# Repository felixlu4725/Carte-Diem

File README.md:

# Carte Diem - Smart Shopping Cart 

## [Product Demo Video](https://youtu.be/1DGey0mXCpI?si=HsvZ1QVfaDtIknsd)

Carte Diem is a add-on module that integrates smart features to regular carts. This device eliminates the need for checkout lines while maintaining anti-theft features. It’s modularity allows stores to easily implement this technology into the existing ecosystems.

### README Directories
- [PCB](PCB/README.md) — schematics, layout, and power architecture  
- [CAD](CAD/README.md) — mechanical enclosures and mounting hardware
- [cart](cart/README.md) - UI interfacing and backend servers
- [cart_tracking](cart_tracking/README.md) - frontend and backend server for cart tracking
- [Integration](integration/README.md) — ESP32 ↔ Raspberry Pi integration and BLE communication

## Motivation

Despite the widespread adoption of self-checkout, grocery stores still experience congestion, long wait times, and loss-prevention challenges. Existing smart cart solutions address these issues but come at a cost of **$5,000–$10,000 per cart**, making large-scale deployment unrealistic for most retailers.

Carte Diem explores a different design space:
- Retrofit instead of full cart replacement  
- Sensor fusion instead of single-modality detection  
- Real-time embedded verification instead of post-hoc auditing  

The goal is to eliminate checkout lines entirely while maintaining store-side trust, scalability, and cost efficiency.

---

## System Overview

Carte Diem consists of two tightly coupled subsystems:

### On-Cart Embedded System
- **Custom ESP32-S3 PCB** running FreeRTOS
- Interfaces with all sensors and peripherals
- Performs real-time sensing, verification, and event generation
- Communicates with the Raspberry Pi via BLE

### On-Cart Compute + Backend
- **Raspberry Pi 4** provides UI, networking, and payment flow
- Connects to store and Carte Diem servers over WiFi
- Handles inventory queries, checkout confirmation, and analytics upload

---

## Key Features

### Item Detection & Verification
- **Barcode Scanning**
  - Primary item identification method
  - Button- or proximity-triggered
  - Fast and reliable for most items

- **RFID Item Verification**
  - Detects tagged items (e.g., alcohol, high-value goods)
  - Automatically cross-checks cart contents
  - Flags unscanned additions in real time

- **Weight-Based Verification**
  - Four load cells under the cart basket
  - Cross-checks expected vs. measured weight
  - Detects unscanned add/remove events
  - Freezes checkout when inconsistencies are detected

- **Produce Scale**
  - Dedicated top-mounted scale
  - Computes price dynamically based on weight

### Checkout & Security
- **Checkout & Payment**
  - Simulated RFID tap-to-pay
  - QR-code payment flow (Square API)
  - Digital receipt generation

- **GPS-Based Security**
  - Store-defined cart boundaries
  - Alarm triggered if cart exits allowed area

### Analytics & Store Insights
- **Cart Tracking**
  - RFID-based indoor tracking (no computer vision)
  - Generates cart paths and heatmaps
  - Aggregates multi-session shopping behavior

---

## Hardware Architecture

- Custom **ESP32-S3 PCB**
  - UART: barcode scanner, RFID modules
  - SPI: payment RFID
  - I²C: IMU, proximity sensor
  - ADC + GPIO: load cells
  - BLE: ESP32 ↔ Raspberry Pi
- Raspberry Pi 4 with touchscreen display
- Dedicated **12 V LiFePO₄ battery**
- Multi-rail power system (12 V, 9 V, 5 V, 3.3 V, 1.8 V)
- 3D-printed enclosures designed for durability and weather resistance

The system is designed to operate **15+ hours continuously**, matching a full day of store operation.

---

## Software Architecture

- **FreeRTOS-based firmware**
  - Periodic tasks for sensing and monitoring
  - Event-driven verification triggered by weight changes
  - ISR-to-task deferral for responsiveness and power efficiency

- **BLE Communication Protocol**
  - Structured commands for barcode scans, weight readings, RFID bursts, and cart tracking logs

- **Full-Stack Web Backend**
  - Store database and inventory management
  - Cart registration and session tracking
  - Heatmap and path visualization
  - GPS boundary configuration interface

---

## Repository Structure

```text
.
├── CAD/               # Mechanical CAD files for enclosures and mounts
├── PCB/               # Schematics, PCB layouts, and fabrication files
├── cart/              # On-cart UI (Raspberry Pi touchscreen interface)
├── integration/       # ESP32 ↔ Raspberry Pi integration and BLE logic
├── LICENSE            # GPL-3.0 license
└── README.md

```

## Results

- Fully functional prototype demonstrated at the EECS Design Expo
- Reliable real-time detection of item add/remove events using sensor fusion
- Weight-based verification successfully detected unscanned items
- RFID-based cart tracking enabled path reconstruction and heatmap generation
- End-to-end checkout flow validated, including UI, payment simulation, and receipt generation
- Power system met full-day operation targets under worst-case load conditions

## Photo Dump

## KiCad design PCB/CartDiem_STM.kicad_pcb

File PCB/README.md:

# Carte Diem — PCB

This directory contains the **custom ESP32-S3-based PCB** designed for the Carte Diem smart shopping cart system.  
The board serves as the central embedded controller, interfacing with all on-cart sensors, peripherals, and the Raspberry Pi.

---

## Overview

The PCB is responsible for:
- Real-time sensor acquisition
- Item verification and cart state monitoring
- Power distribution and regulation
- BLE communication with the Raspberry Pi

It was designed to support **all-day operation**, modular peripherals, and reliable performance in a noisy retail environment.

---

## Manufractured PCB

## Key Features

- **ESP32-S3 MCU**
  - Runs FreeRTOS
  - Handles sensing, control, and BLE communication

- **Peripheral Interfaces**
  - UART: barcode scanner, item RFID, cart-tracking RFID
  - SPI: payment RFID module
  - I²C: IMU, proximity sensor
  - GPIO + ADC: load cells (via HX711)

- **Power Architecture**
  - 12 V input (external battery)
  - On-board buck and LDO regulation
  - Supports 12 V, 9 V, 5 V, 3.3 V, and 1.8 V rails

- **Connectivity**
  - BLE for bidirectional communication with Raspberry Pi
  - Dedicated connectors for modular sensor attachment

---

## Design Notes

- EMI mitigation was required due to proximity of RFID modules and load cells  
- Power paths were designed conservatively to support peak current draw  
- The board went through multiple revisions to resolve rail shorting and voltage tolerance issues  

---

## Schematic

### Top level

### Power Distribution

### Integrated IMU

### Routing

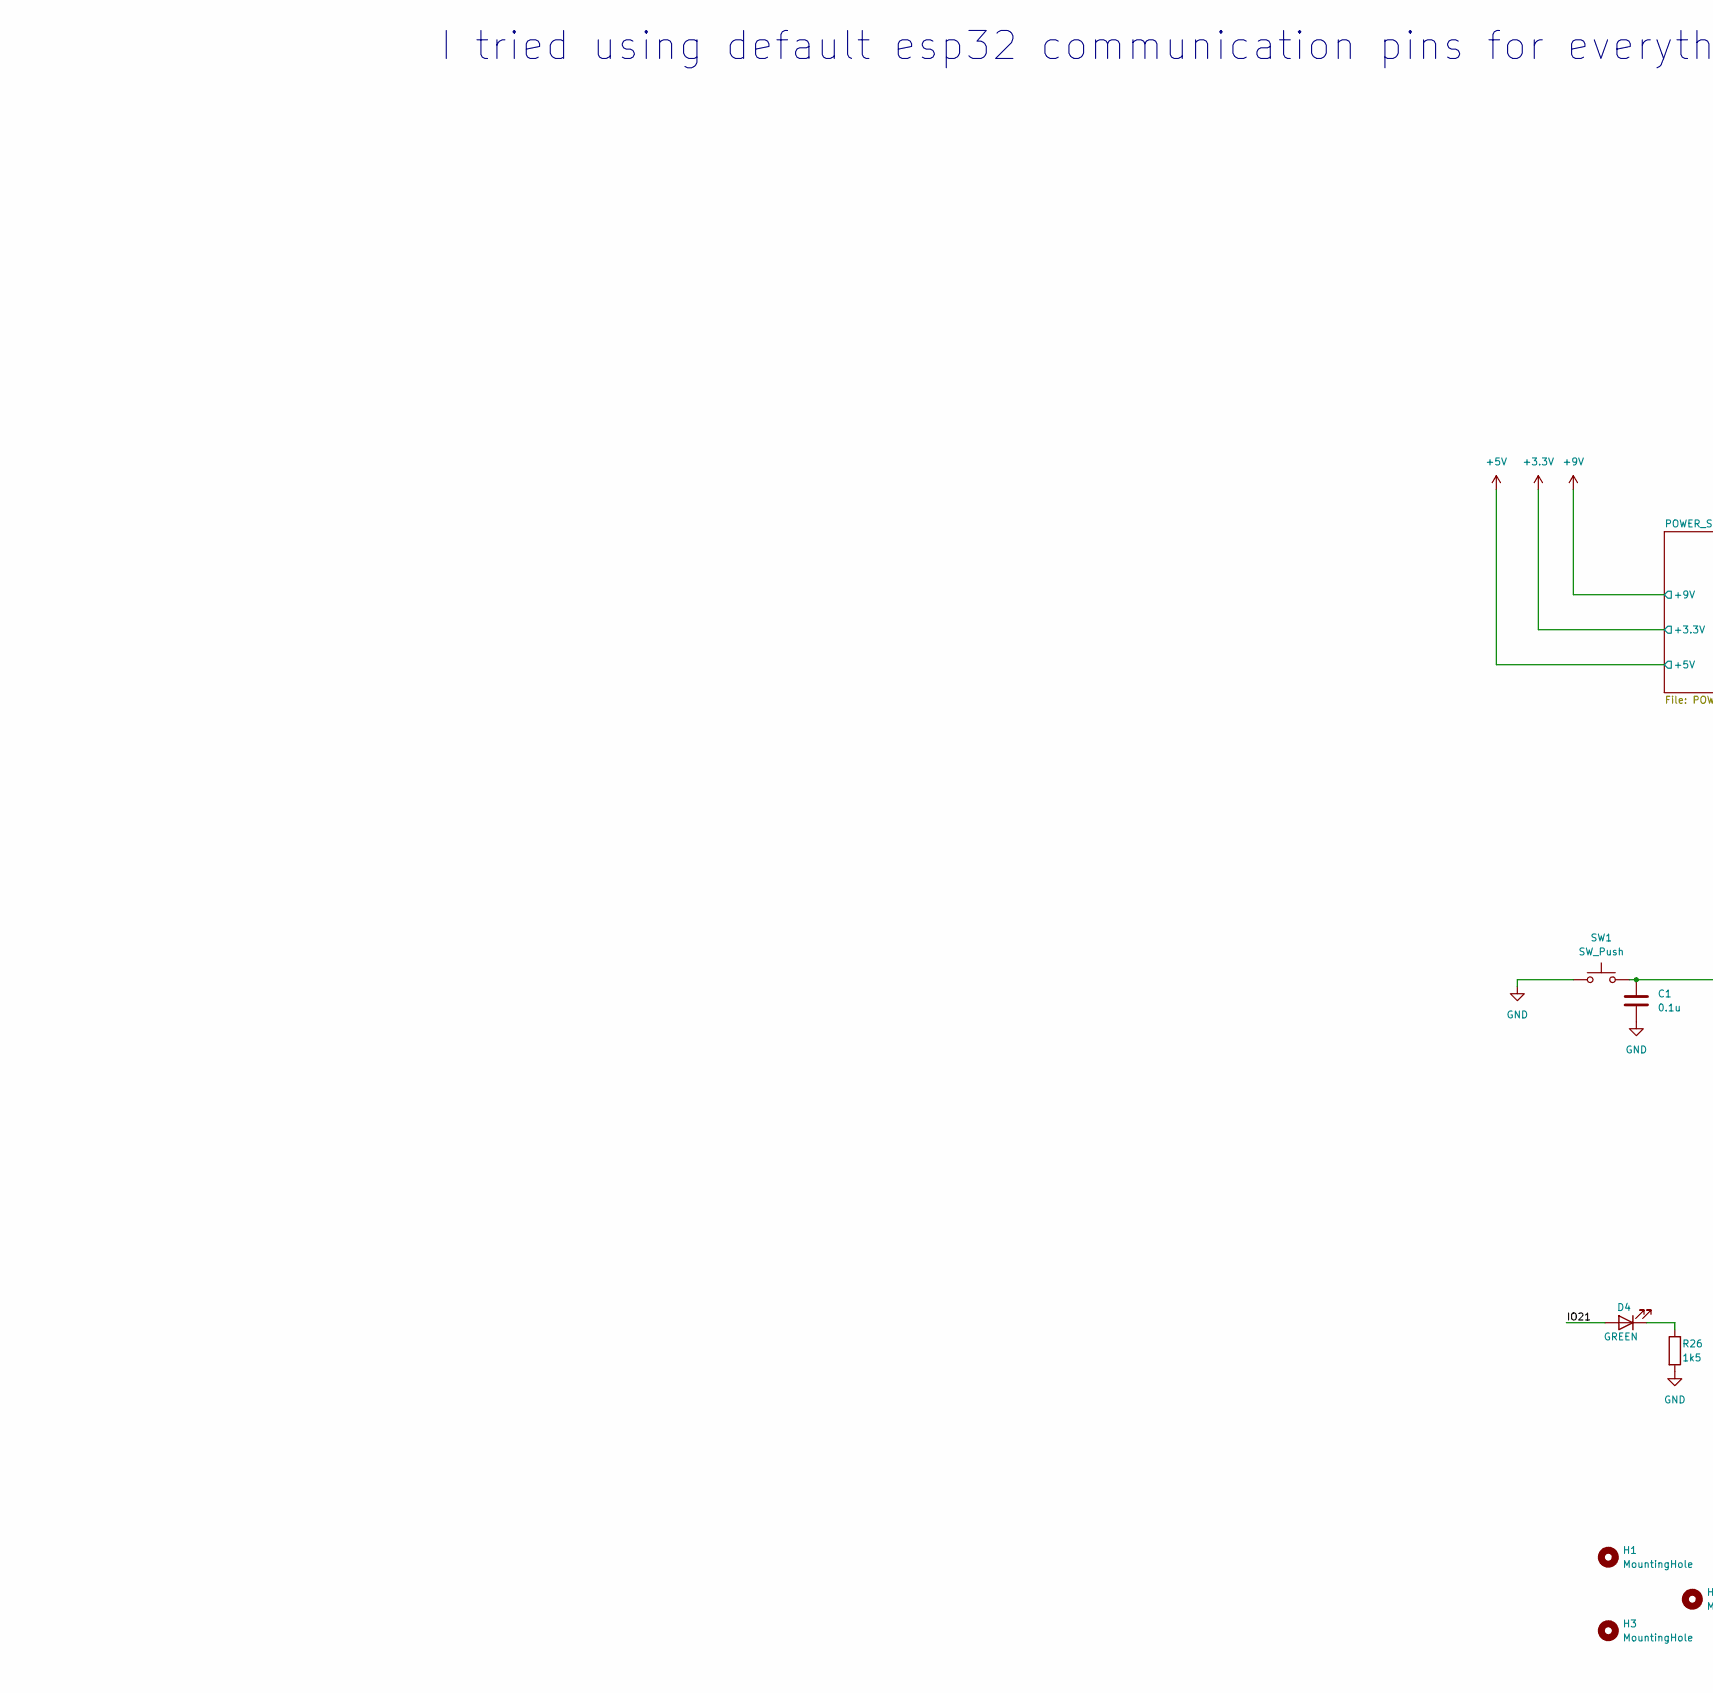
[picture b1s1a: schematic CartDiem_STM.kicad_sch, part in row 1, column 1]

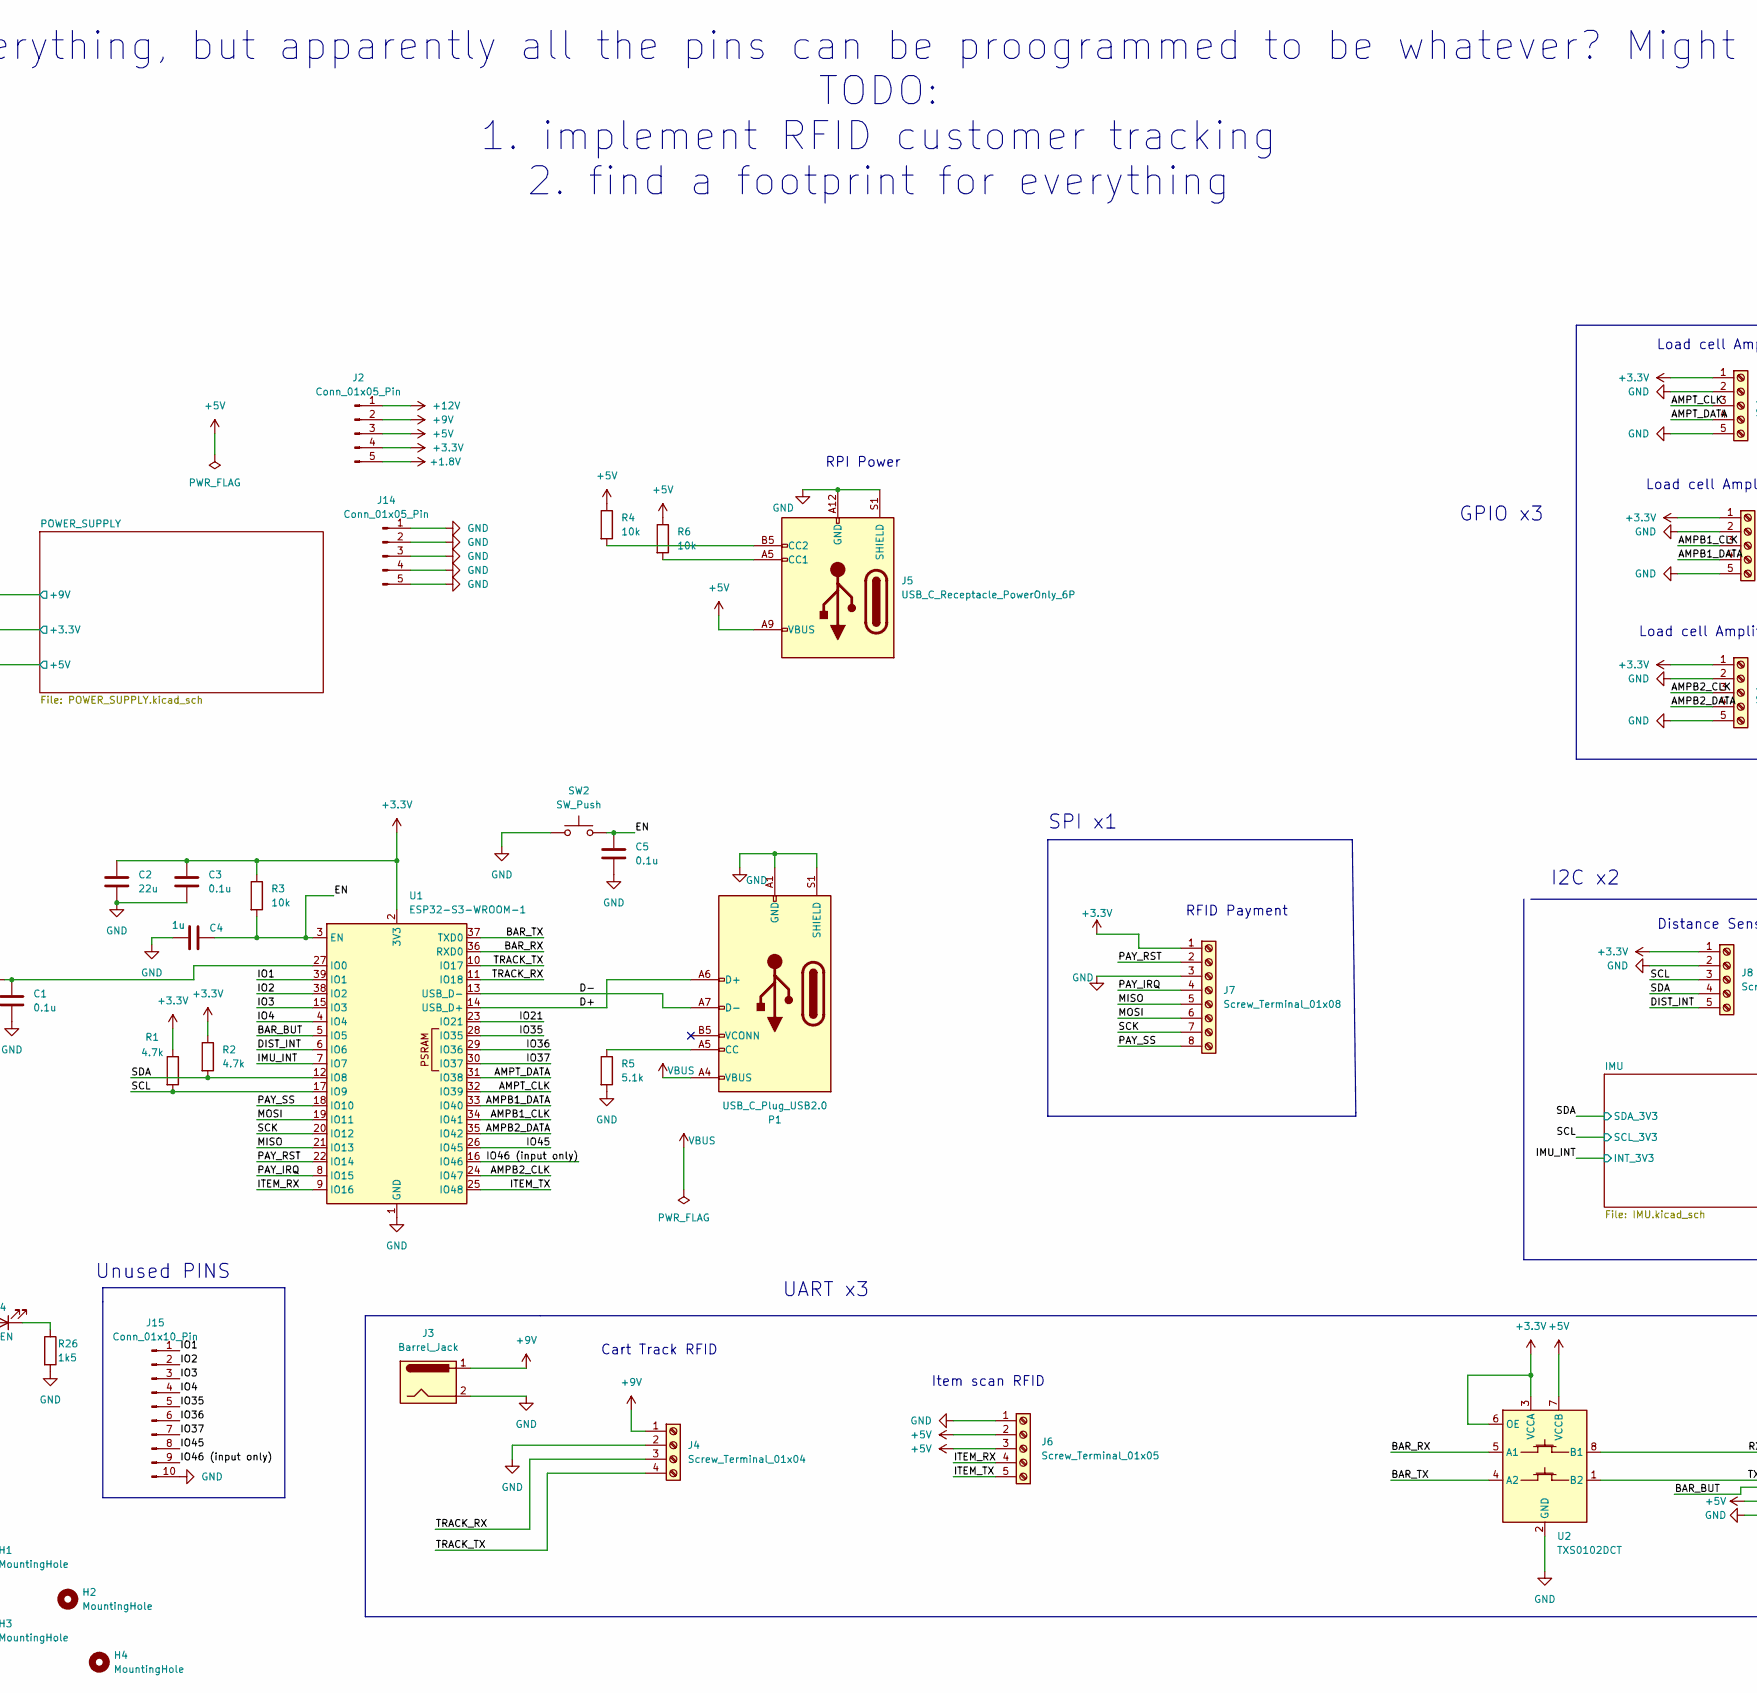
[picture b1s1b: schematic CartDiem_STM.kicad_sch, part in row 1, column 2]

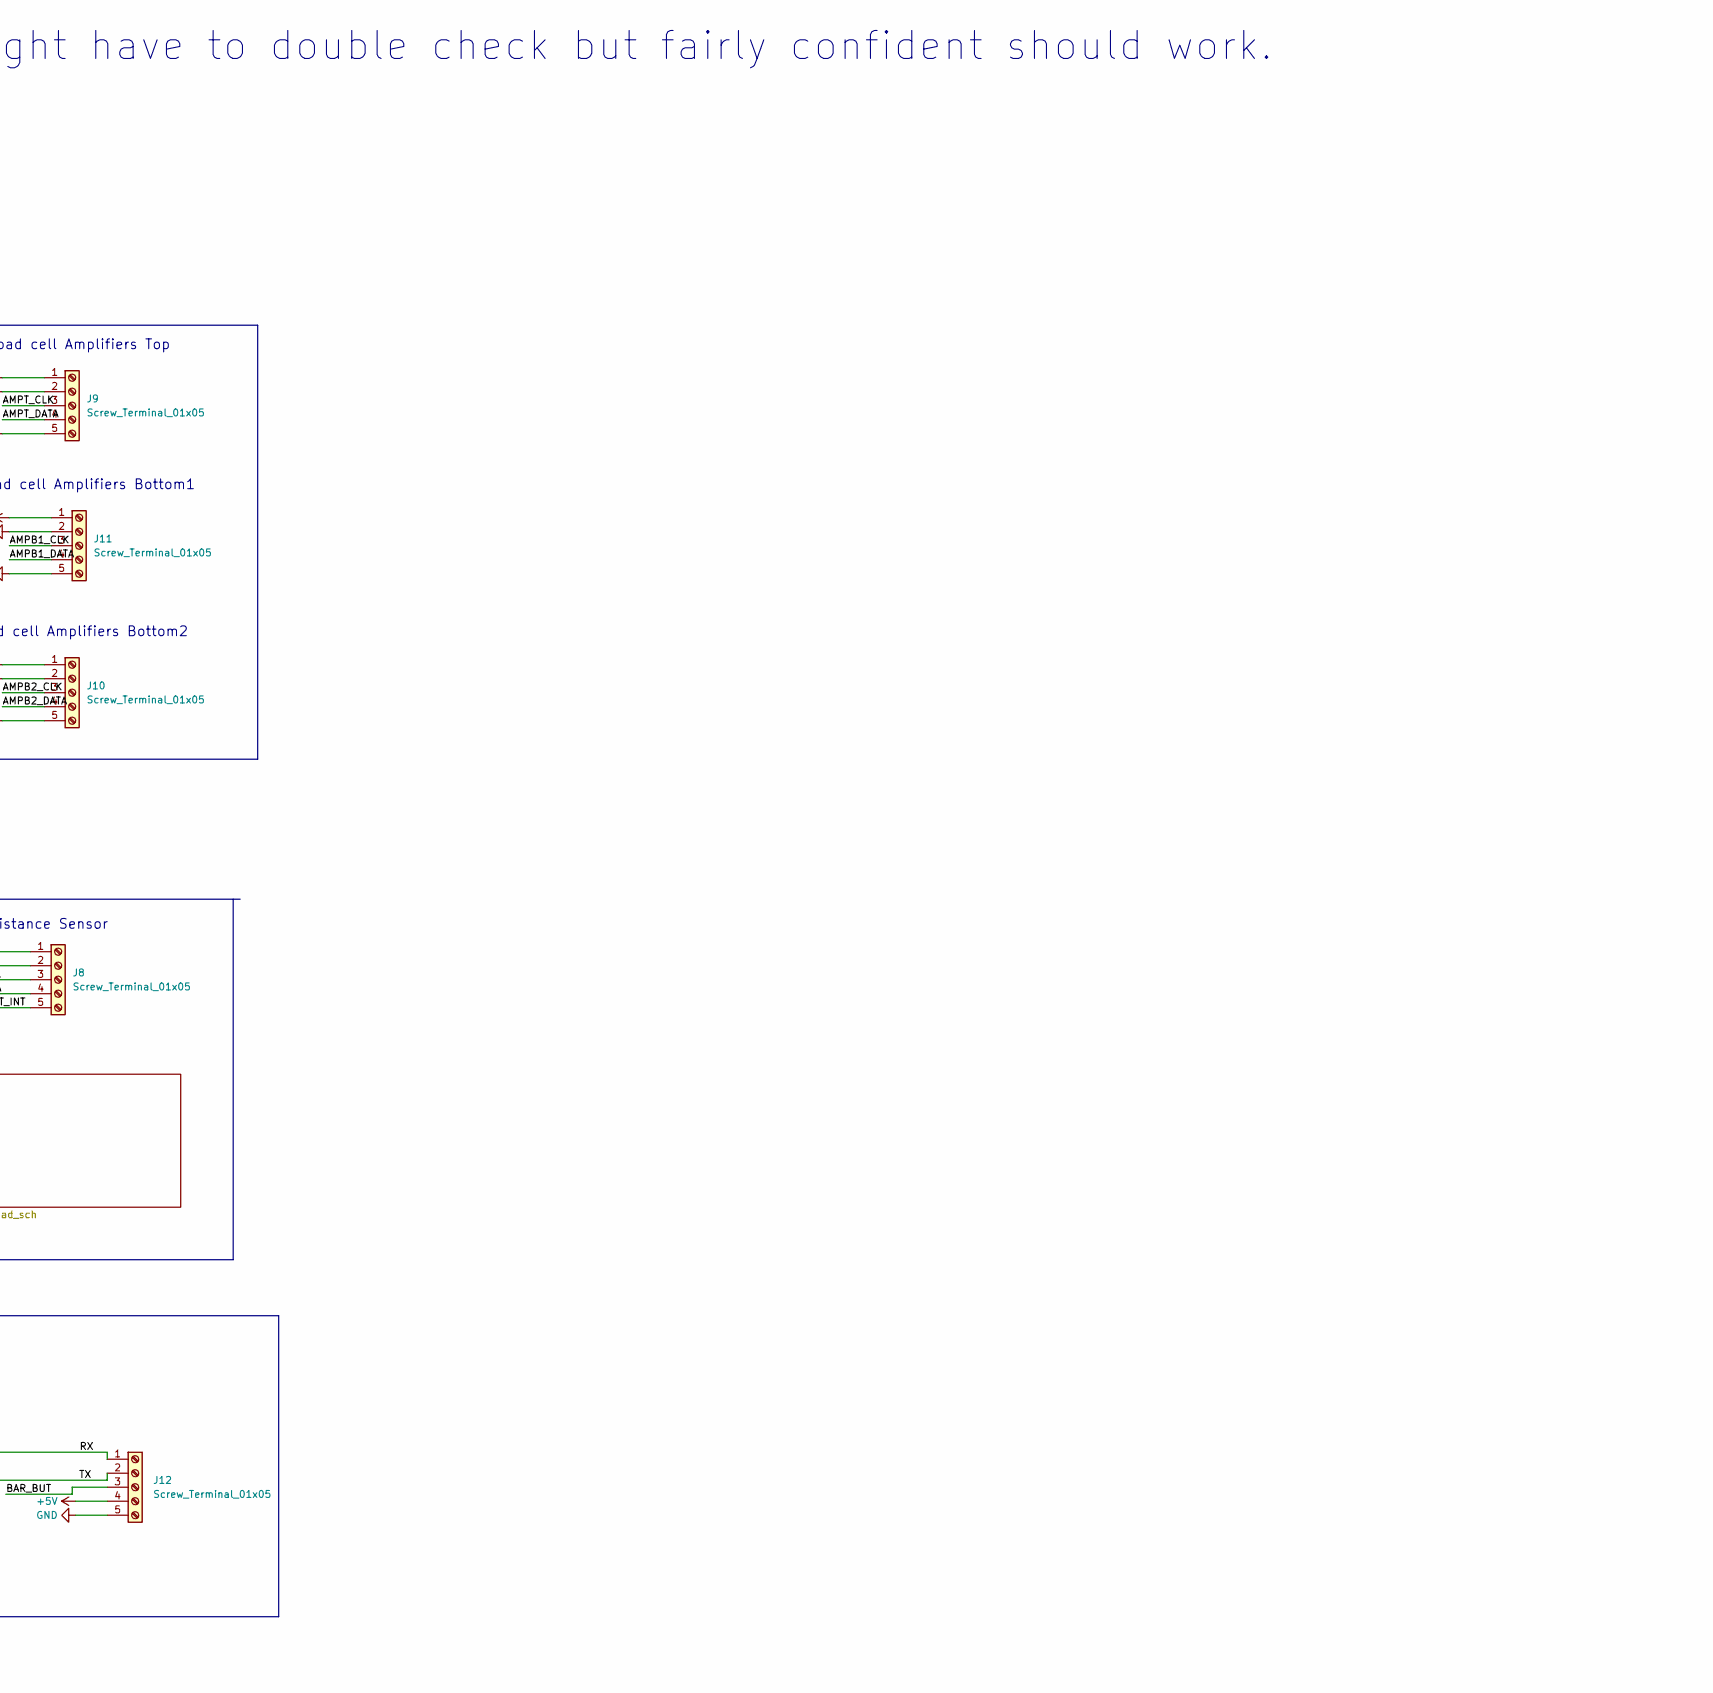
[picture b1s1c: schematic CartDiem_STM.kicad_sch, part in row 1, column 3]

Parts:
C1, C3, C5: 0.1u; C_0603_1608Metric
C2: 22u; C_1210_3225Metric
C4: 1u; C_0603_1608Metric
D4: GREEN; LED_0603_1608Metric
H1, H2, H3, H4: MountingHole; MountingHole_3.2mm_M3
J2, J14: Conn_01x05_Pin; PinHeader_1x05_P2.54mm_Vertical
J3: Barrel_Jack; BarrelJack_CUI_PJ-063AH_Horizontal
J4: Screw_Terminal_01x04; TerminalBlock_Xinya_XY308-2.54-4P_1x04_P2.54mm_Horizontal
J5: USB_C_Receptacle_PowerOnly_6P; USB_C_Receptacle_GCT_USB4125-xx-x-0190_6P_TopMnt_Horizontal
J6, J8, J9, J10, J11, J12: Screw_Terminal_01x05; TerminalBlock_Xinya_XY308-2.54-5P_1x05_P2.54mm_Horizontal
J7: Screw_Terminal_01x08; TerminalBlock_Xinya_XY308-2.54-8P_1x08_P2.54mm_Horizontal
J15: Conn_01x10_Pin; PinHeader_1x10_P2.54mm_Vertical
P1: USB_C_Plug_USB2.0; GCT_USB4120-03-C_REVA
R1, R2: 4.7k; R_0603_1608Metric
R3, R4, R6: 10k; R_0603_1608Metric
R5: 5.1k; R_0603_1608Metric
R26: 1k5; R_0603_1608Metric
SW1, SW2: SW_Push; SW_Push_1P1T_XKB_TS-1187A
U1: ESP32-S3-WROOM-1
U2: TXS0102DCT; SSOP-8_2.95x2.8mm_P0.65mm

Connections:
+1.8V: J2.5; also elsewhere on the board
+3.3V: C2.1, C3.1, J2.4, J7.1, J8.1, J9.1, J10.1, J11.1, R1.1, R2.1, R3.1, U1.2 (3V3), U2.3 (VCCA), U2.6 (OE); also elsewhere on the board
+5V: J2.3, J5.A9 (VBUS), J5.B9 (VBUS), J6.2, J6.3, J12.4, R4.1, R6.1, U2.7 (VCCB); also elsewhere on the board
+9V: J2.2, J3.1, J4.1; also elsewhere on the board
+12V: J2.1; also elsewhere on the board
/AMPB1_CLK: J11.3, U1.34 (IO41)
/AMPB1_DATA: J11.4, U1.33 (IO40)
/AMPB2_CLK: J10.3, U1.24 (IO47)
/AMPB2_DATA: J10.4, U1.35 (IO42)
/AMPT_CLK: J9.3, U1.32 (IO39)
/AMPT_DATA: J9.4, U1.31 (IO38)
/BAR_BUT: J12.3, U1.5 (IO5)
/BAR_RX: U1.36 (RXD0), U2.5 (A1)
/BAR_TX: U1.37 (TXD0), U2.4 (A2)
/D+: P1.A6 (D+), U1.14 (USB_D+)
/D-: P1.A7 (D-), U1.13 (USB_D-)
/DIST_INT: J8.5, U1.6 (IO6)
/EN: C4.2, C5.1, R3.2, SW2.2, U1.3 (EN)
/IMU_INT: U1.7 (IO7); also elsewhere on the board
/IO1: J15.1, U1.39 (IO1)
/IO2: J15.2, U1.38 (IO2)
/IO3: J15.3, U1.15 (IO3)
/IO4: J15.4, U1.4 (IO4)
/IO21: D4.2 (A), U1.23 (IO21)
/IO35: J15.5, U1.28 (IO35)
/IO36: J15.6, U1.29 (IO36)
/IO37: J15.7, U1.30 (IO37)
/IO45: J15.8, U1.26 (IO45)
/IO46 (input only): J15.9, U1.16 (IO46)
/ITEM_RX: J6.4, U1.9 (IO16)
/ITEM_TX: J6.5, U1.25 (IO48)
/MISO: J7.5, U1.21 (IO13)
/MOSI: J7.6, U1.19 (IO11)
/PAY_IRQ: J7.4, U1.8 (IO15)
/PAY_RST: J7.2, U1.22 (IO14)
/PAY_SS: J7.8, U1.18 (IO10)
/RX: J12.1, U2.8 (B1)
/SCK: J7.7, U1.20 (IO12)
/SCL: J8.3, R1.2, U1.17 (IO9); also elsewhere on the board
/SDA: J8.4, R2.2, U1.12 (IO8); also elsewhere on the board
/TRACK_RX: J4.3, U1.11 (IO18)
/TRACK_TX: J4.4, U1.10 (IO17)
/TX: J12.2, U2.1 (B2)
GND: C1.2, C2.2, C3.2, C4.1, C5.2, J3.2, J4.2, J5.A12 (GND), J5.B12 (GND), J5.S1 (SHIELD), J6.1, J7.3, J8.2, J9.2, J9.5, J10.2, J10.5, J11.2, J11.5, J12.5, J14.1, J14.2, J14.3, J14.4, J14.5, J15.10, P1.A1 (GND), P1.A12 (GND), P1.B1 (GND), P1.B12 (GND), P1.S1 (SHIELD), R5.2, R26.2, SW1.1, SW2.1, U1.1 (GND), U1.40 (GND), U1.41 (GND), U2.2 (GND); also elsewhere on the board
unnamed: D4.1 (K), R26.1
unnamed: J5.A5 (CC1), R6.2
unnamed: J5.B5 (CC2), R4.2
unnamed: P1.A5 (CC), R5.1
unnamed: C1.1, SW1.2, U1.27 (IO0)
VBUS: P1.A4 (VBUS), P1.A9 (VBUS), P1.B4 (VBUS), P1.B9 (VBUS); also elsewhere on the board

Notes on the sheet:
Item scan RFID
Unused PINS
Load cell Amplifiers Bottom2
RFID Payment
Cart Track RFID
Distance Sensor
SPI x1
Load cell Amplifiers Bottom1
UART x3
I tried using default esp32 communication pins for everything, but apparently all the pins can be proogrammed to be whatever? Might have to double check but fairly confident should work. TODO: 1. implement RFID customer tracking 2. find a footprint for everything
Load cell Amplifiers Top
GPIO x3
RPI Power
I2C x2

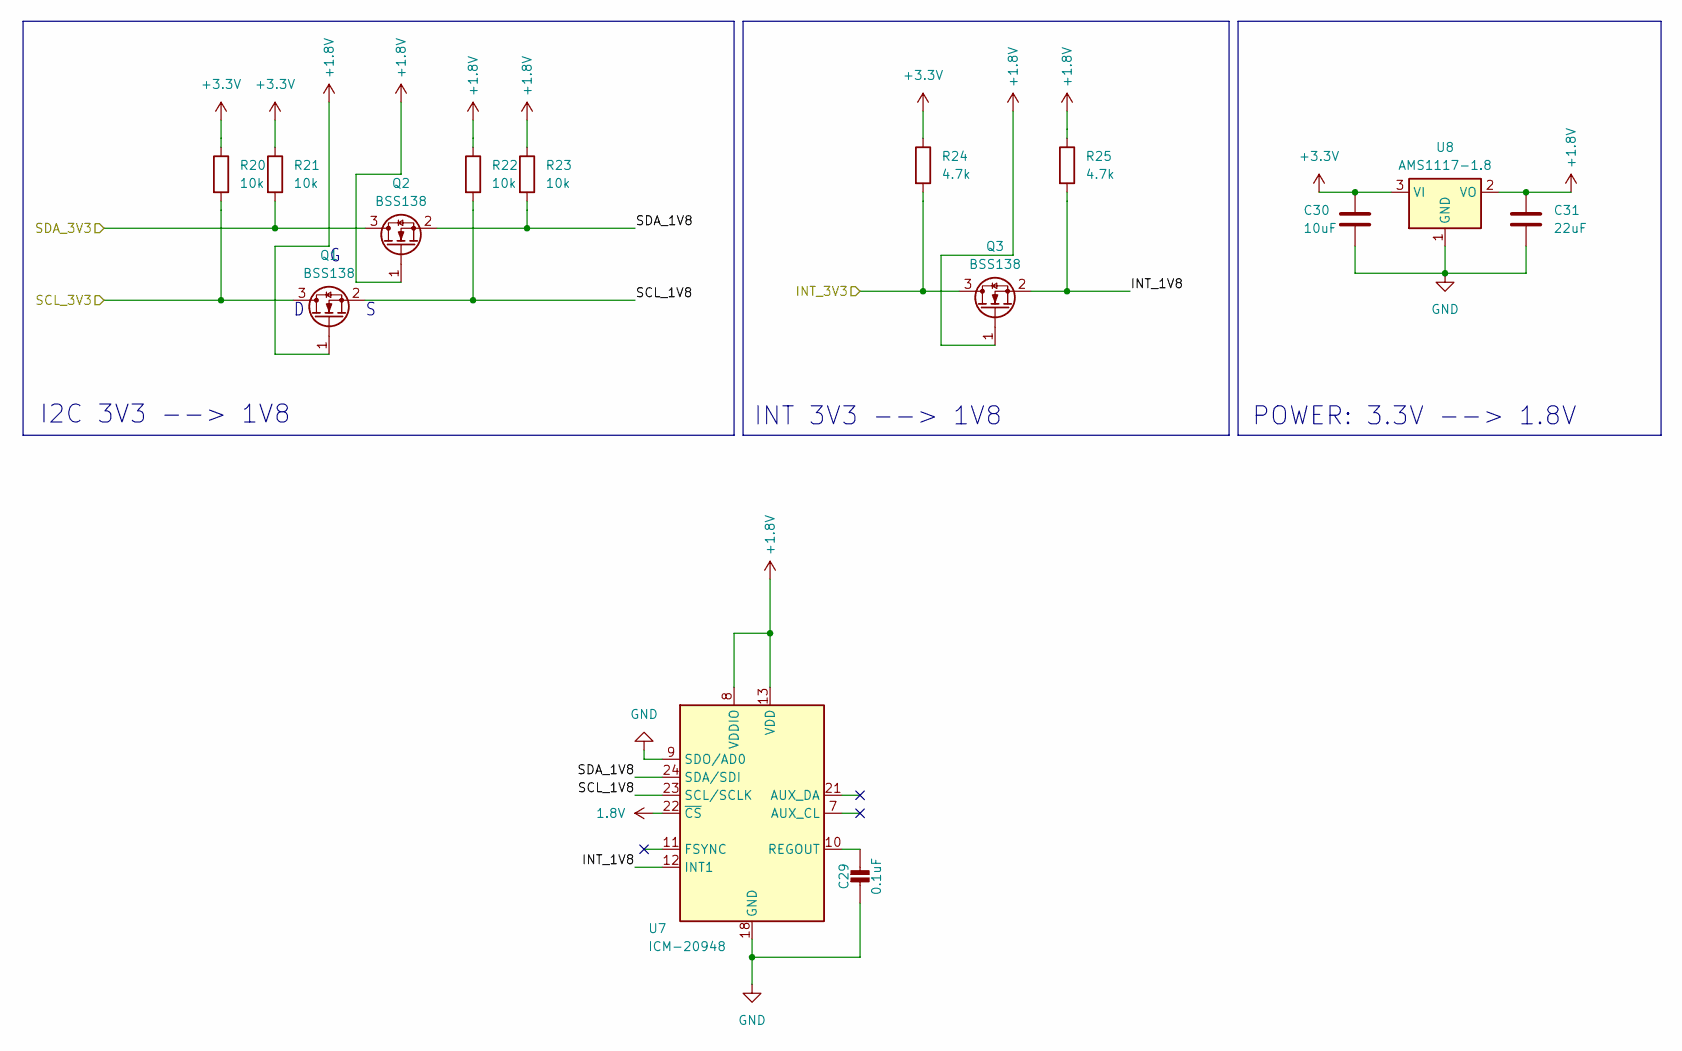
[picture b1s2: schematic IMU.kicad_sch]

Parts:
C29: 0.1uF; C_0603_1608Metric
C30: 10uF; C_0805_2012Metric
C31: 22uF; C_1210_3225Metric
Q1, Q2, Q3: BSS138; SOT-23
R20, R21, R22, R23: 10k; R_0603_1608Metric
R24, R25: 4.7k; R_0603_1608Metric
U7: ICM-20948; InvenSense_QFN-24_3x3mm_P0.4mm
U8: AMS1117-1.8; SOT-223-3_TabPin2

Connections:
1.8V: U7.22 (~CS)
+1.8V: C31.1, Q1.1 (G), Q2.1 (G), Q3.1 (G), R22.1, R23.1, R25.1, U7.8 (VDDIO), U7.13 (VDD), U8.2 (VO); also elsewhere on the board
+3.3V: C30.2, R20.1, R21.1, R24.1, U8.3 (VI); also elsewhere on the board
/IMU/INT_1V8: Q3.2 (S), R25.2, U7.12 (INT1)
/IMU/SCL_1V8: Q1.2 (S), R22.2, U7.23 (SCL/SCLK)
/IMU/SDA_1V8: Q2.2 (S), R23.2, U7.24 (SDA/SDI)
/IMU_INT: Q3.3 (D), R24.2; also elsewhere on the board
/SCL: Q1.3 (D), R20.2; also elsewhere on the board
/SDA: Q2.3 (D), R21.2; also elsewhere on the board
GND: C29.2, C30.1, C31.2, U7.9 (SDO/AD0), U7.18 (GND), U7.20 (GND), U8.1 (GND); also elsewhere on the board
unnamed: C29.1, U7.10 (REGOUT)

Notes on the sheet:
I2C 3V3 --> 1V8
INT 3V3 --> 1V8
POWER: 3.3V --> 1.8V

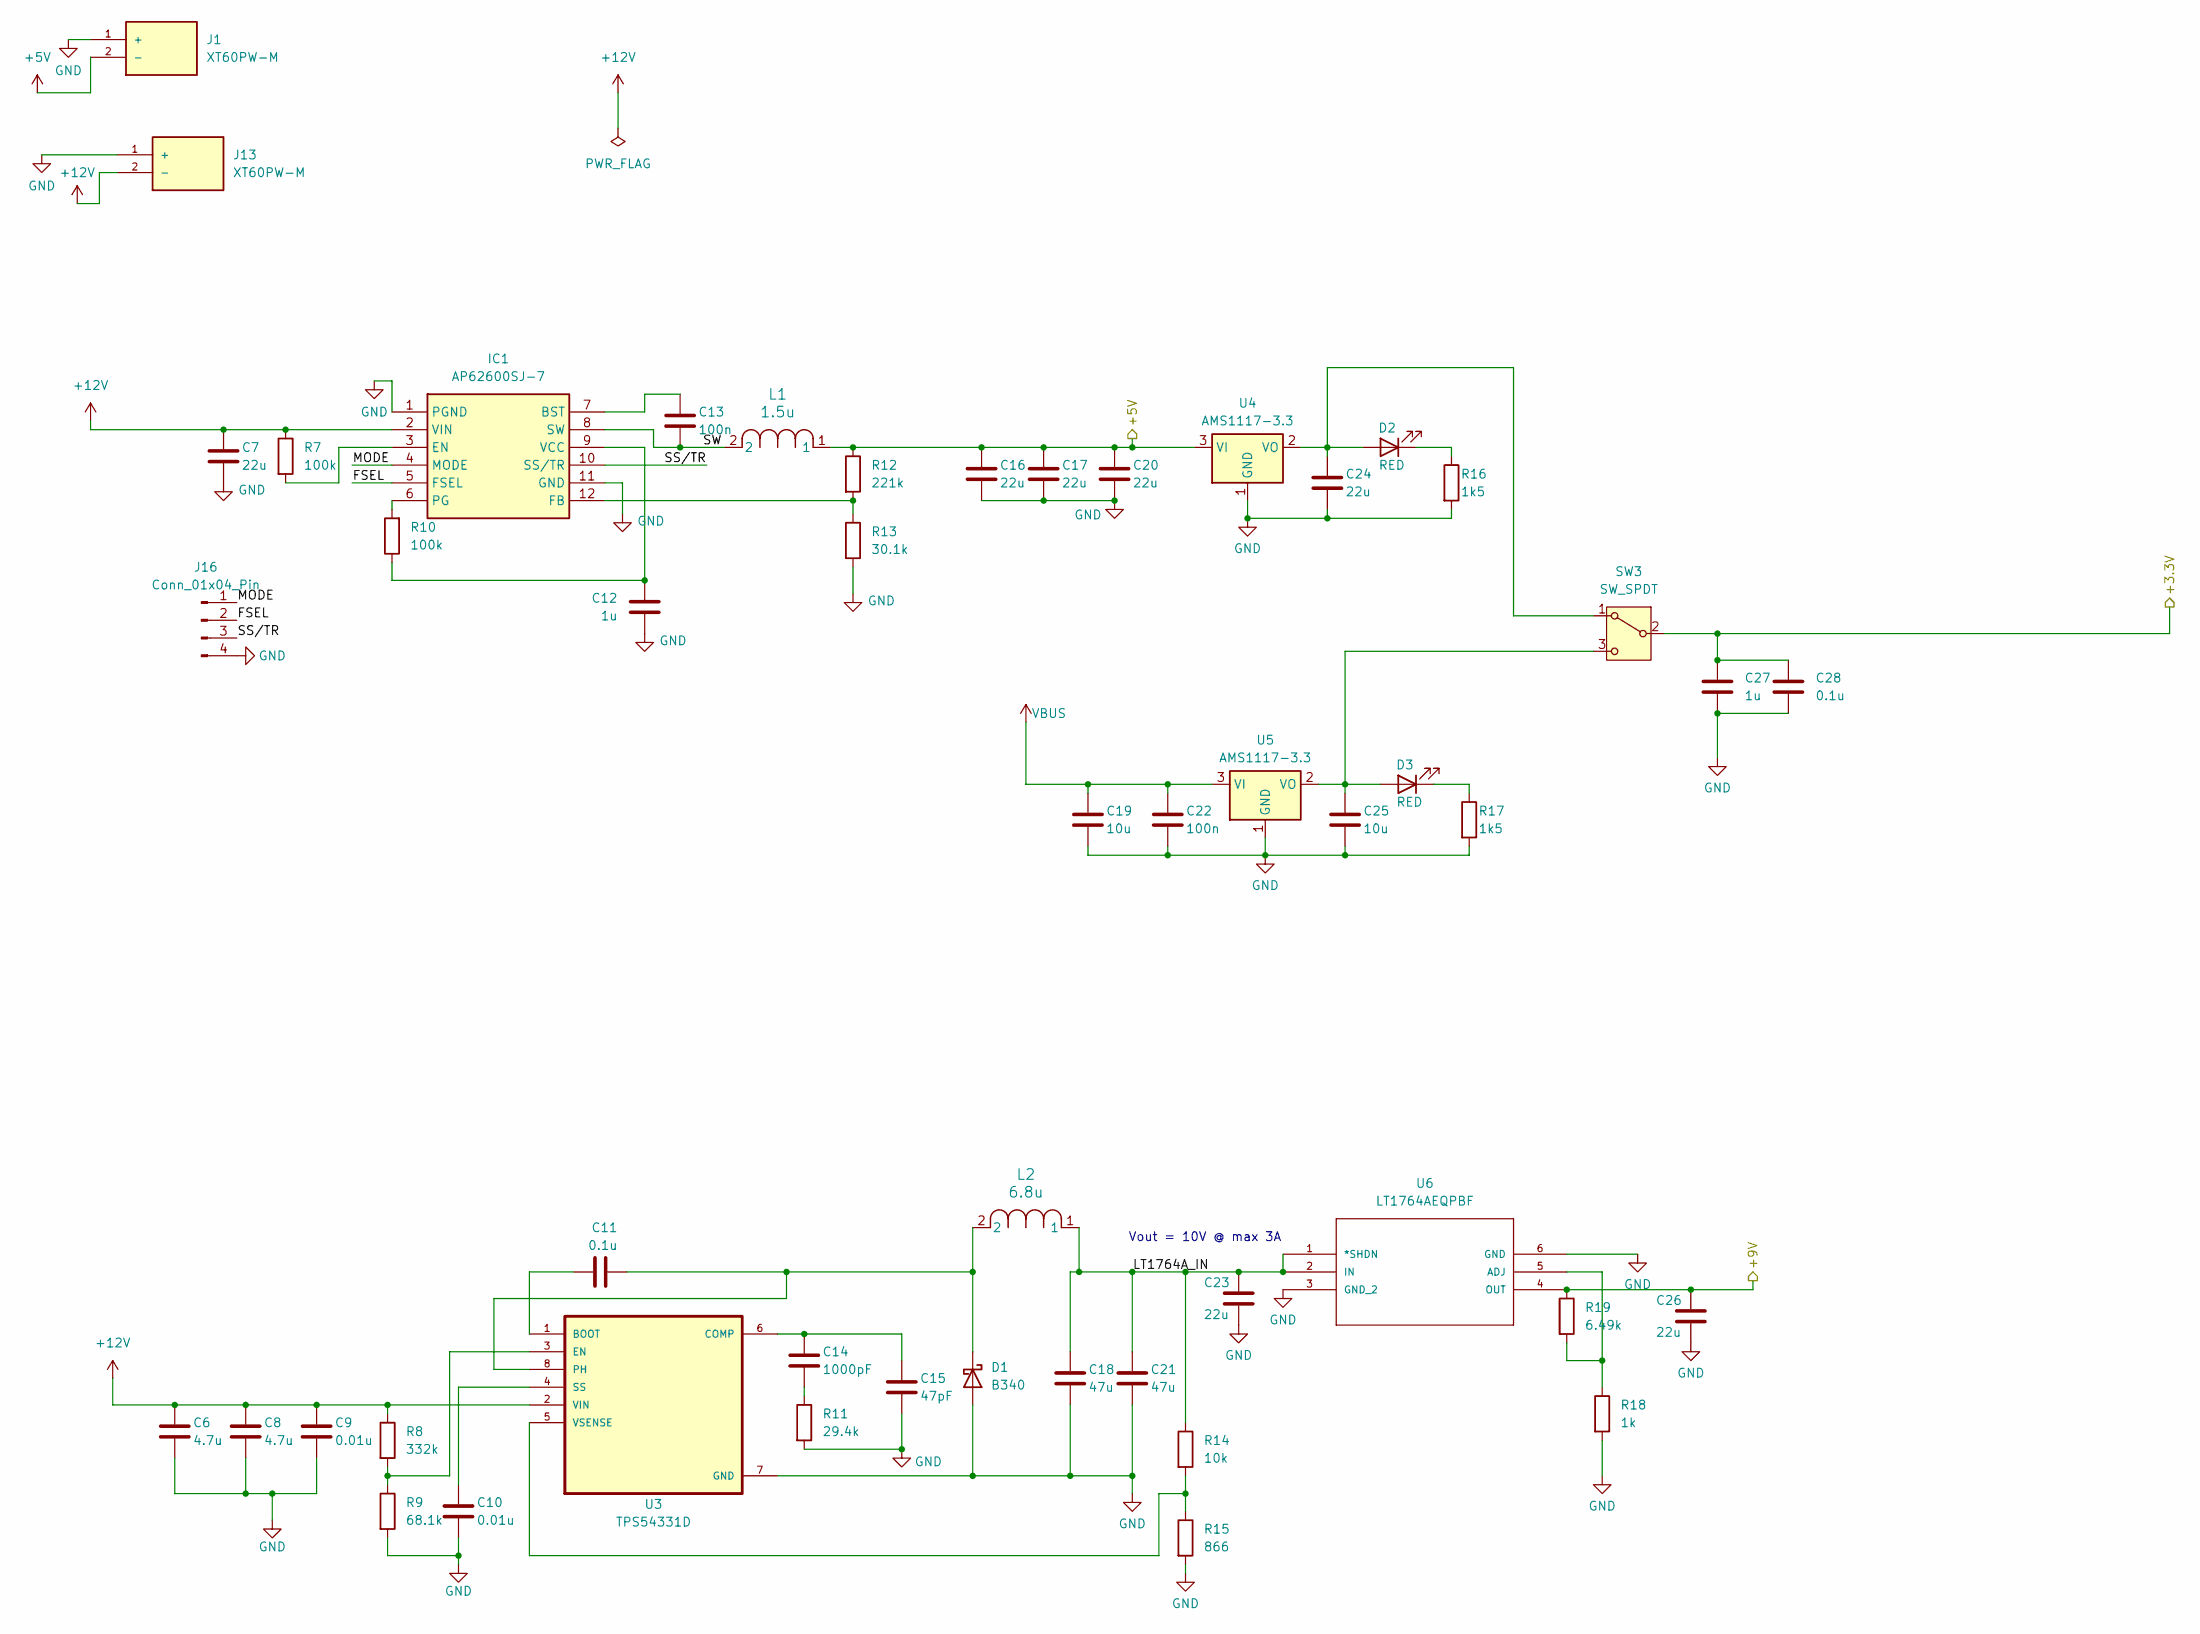
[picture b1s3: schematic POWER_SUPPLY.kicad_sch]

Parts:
C6, C8: 4.7u; C_0805_2012Metric
C7, C16, C17, C20: 22u; C_1210_3225Metric
C9, C10: 0.01u; C_0603_1608Metric
C11, C28: 0.1u; C_0603_1608Metric
C12, C27: 1u; C_0603_1608Metric
C13, C22: 100n; C_0805_2012Metric
C14: 1000pF; C_0603_1608Metric
C15: 47pF; C_0603_1608Metric
C18, C21: 47u; C_1210_3225Metric
C19, C25: 10u; C_0805_2012Metric
C23, C26: 22u; C_1206_3216Metric
C24: 22u; C_0805_2012Metric
D1: B340; D_SMC
D2, D3: RED; LED_0603_1608Metric
IC1: AP62600SJ-7; AP62600SJ7; Manufacturer_Part_Number AP62600SJ-7; Mouser Part Number 621-AP62600SJ-7
J1, J13: XT60PW-M; AMASS_XT60IPW-M_1x03_P7.20mm_Horizontal; PARTREV V1.2
J16: Conn_01x04_Pin; PinSocket_1x04_P2.54mm_Vertical
L1: 1.5u; L_Bourns_SRP6060FA
L2: 6.8u; L_Bourns_SRP6060FA
R7: 100k; R_0805_2012Metric
R8: 332k; R_0805_2012Metric
R9: 68.1k; R_0805_2012Metric
R10: 100k; R_0603_1608Metric
R11: 29.4k; R_0603_1608Metric
R12: 221k; R_0603_1608Metric
R13: 30.1k; R_0603_1608Metric
R14: 10k; R_0603_1608Metric
R15: 866; R_0603_1608Metric
R16, R17: 1k5; R_0603_1608Metric
R18: 1k; R_0603_1608Metric
R19: 6.49k; R_0603_1608Metric
SW3: SW_SPDT; SW_SPDT_PCM12
U3: TPS54331D; SOIC127P599X175-8N
U4, U5: AMS1117-3.3; SOT-223-3_TabPin2
U6: LT1764AEQPBF; DDPAK-5_Q; MANUFACTURER_PART_NUMBER LT1764AEQ#PBF; DIGIKEY_PART_NUMBER LT1764AEQ#PBFND

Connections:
+3.3V: C27.1, C28.1, SW3.2 (B); also elsewhere on the board
+5V: C16.1, C17.1, C20.1, J1.2 (-), L1.1, R12.1, U4.3 (VI); also elsewhere on the board
+9V: C26.1, R19.1, U6.4 (OUT); also elsewhere on the board
+12V: C6.1, C7.1, C8.1, C9.1, IC1.2 (VIN), J13.2 (-), R7.1, R8.1, U3.2 (VIN); also elsewhere on the board
/POWER_SUPPLY/FSEL: IC1.5 (FSEL), J16.2
/POWER_SUPPLY/LT1764A_IN: C18.1, C21.1, C23.1, L2.1, R14.1, U6.1 (*SHDN), U6.2 (IN)
/POWER_SUPPLY/MODE: IC1.4 (MODE), J16.1
/POWER_SUPPLY/SS/TR: IC1.10 (SS/TR), J16.3
/POWER_SUPPLY/SW: C13.2, IC1.8 (SW), L1.2
GND: C6.2, C7.2, C8.2, C9.2, C10.2, C12.1, C15.2, C16.2, C17.2, C18.2, C19.2, C20.2, C21.2, C22.2, C23.2, C24.2, C25.2, C26.2, C27.2, C28.2, D1.2 (A), IC1.1 (PGND), IC1.11 (GND), J1.1 (+), J13.1 (+), J16.4, R9.2, R11.2, R13.2, R15.2, R16.2, R17.2, R18.2, U3.7 (GND), U4.1 (GND), U5.1 (GND), U6.3 (GND_2), U6.6 (GND); also elsewhere on the board
unnamed: C14.2, R11.1
unnamed: C11.2, D1.1 (K), L2.2, U3.8 (PH)
unnamed: C24.1, D2.2 (A), SW3.1 (A), U4.2 (VO)
unnamed: D2.1 (K), R16.1
unnamed: C25.1, D3.2 (A), SW3.3 (C), U5.2 (VO)
unnamed: D3.1 (K), R17.1
unnamed: C13.1, IC1.7 (BST)
unnamed: IC1.3 (EN), R7.2
unnamed: IC1.12 (FB), R12.2, R13.1
unnamed: IC1.6 (PG), R10.2
unnamed: C12.2, IC1.9 (VCC), R10.1
unnamed: C11.1, U3.1 (BOOT)
unnamed: C14.1, C15.1, U3.6 (COMP)
unnamed: R8.2, R9.1, U3.3 (EN)
unnamed: C10.1, U3.4 (SS)
unnamed: R14.2, R15.1, U3.5 (VSENSE)
unnamed: R18.1, R19.2, U6.5 (ADJ)
VBUS: C19.1, C22.1, U5.3 (VI); also elsewhere on the board

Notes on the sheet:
Vout = 10V @ max 3A

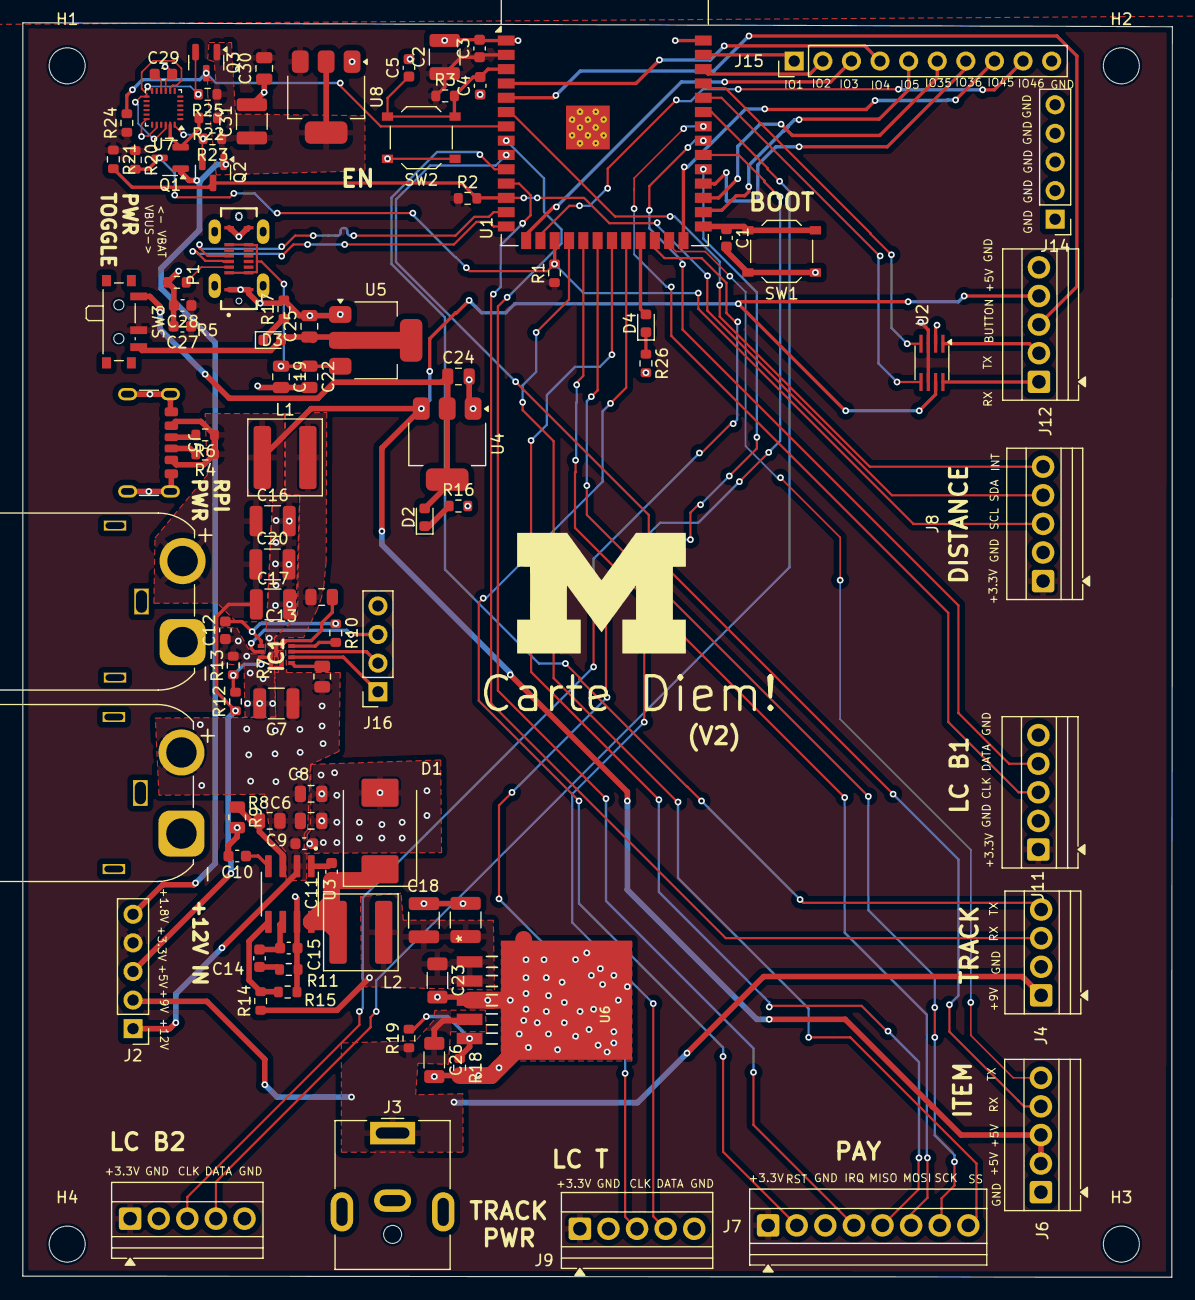
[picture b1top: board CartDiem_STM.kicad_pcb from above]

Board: 2 copper layers, 102.1 x 111.4 mm, 99 parts (0 on the bottom side), 76 nets.

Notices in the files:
parts and their libraries:
COPYRIGHT: Copyright C 2016 Accelerated Designs. All rights reserved
